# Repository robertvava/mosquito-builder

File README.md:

# Drone Club

Custom quadrotor project for hover stability, autonomous 3D movement and an
indoor FPV obstacle course.  The complete system must cost less than £400 and
the same hardware configuration will be used for all three tasks.

## Current component list

- [Revised 4.9-inch build component list](docs/COMPONENT_LIST_4P9_INCH.md)

The root-level `list` file is the working shopping list. The v0.4 CAD below is
a 4.9-inch fit prototype with a mounted Pi and a separately supported battery
tray. Structural and remaining component integration work still remain.

## Current mechanical concept

- [4.9-inch frame with supported Pi and battery v0.4](docs/FRAME_DESIGN_V0_4_PAYLOAD.md)
- [Earlier 4-inch/carbon concept v0.1](docs/FRAME_DESIGN_V0_1.md)
- [Full design and OCP CAD guide](docs/DRONE_DESIGN_AND_OCP_CAD_GUIDE.md)
- [Top review image](cad/exports/frame_top.png)
- [Isometric review image](cad/exports/frame_isometric.png)

Run the interactive build in VS Code with OCP CAD Viewer open:

```bash
uv sync
uv run python -m cad.assembly --show
```

Run checks and regenerate the review/export files:

```bash
uv run python -m unittest discover -s tests -v
uv run python -m cad.assembly --coupons-only
uv run python -m cad.assembly --export
uv run python -m cad.render_svg
uv run python -m cad.render_png
```

The Python files under `cad/` are the design master. Generated STEP/STL and
review images live under `cad/exports/`. Current STEP/STL fit samples and parts
are in `cad/exports/v0_4/`; individual STLs are centred and placed on Z=0.

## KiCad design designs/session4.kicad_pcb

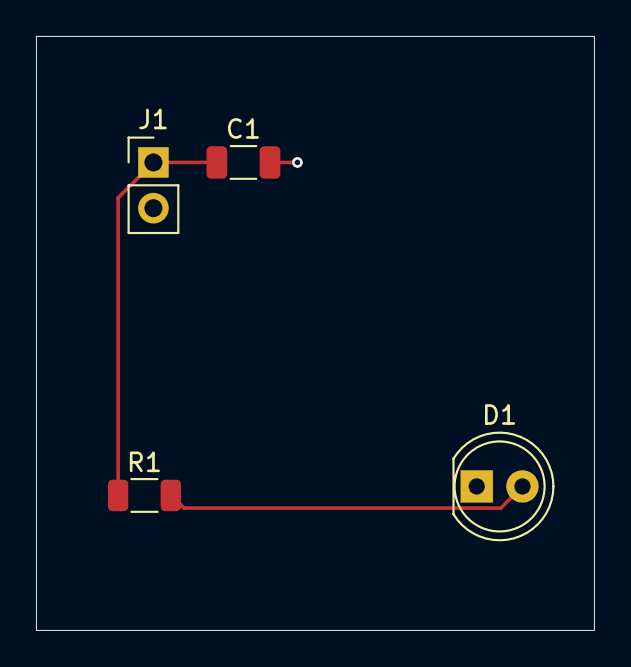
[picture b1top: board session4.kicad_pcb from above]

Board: 2 copper layers, 31.0 x 33.0 mm, 4 parts (0 on the bottom side), 3 nets.

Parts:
C1: 100nF; C_1206_3216Metric
D1: LED_RED; LED_D5.0mm
J1: Conn_01x02_Socket; PinHeader_1x02_P2.54mm_Vertical
R1: 220; R_1206_3216Metric

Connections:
+5V: C1.1, J1.1, R1.1
GND: C1.2, D1.1 (K), J1.2
unnamed: D1.2 (A), R1.2
